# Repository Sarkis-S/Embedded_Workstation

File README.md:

# Embedded Workstation

A compact modular workstation for embedded systems development,
electronics prototyping, hardware testing, and PCB development.

## Current Revision

Rev A is the original acrylic workstation assembled as a practical
development platform rather than from a predefined mechanical design.

Current hardware includes:

- Arduino Uno
- ESP32 development platform
- Solderless breadboards
- Logic analyzer
- External bench power supply support
- Removable prototyping modules
- Two-level acrylic construction for equipment and cable management

## Design Goals

- Keep common embedded-development hardware readily accessible
- Provide a clean breadboarding and experimentation area
- Support both MCU-powered logic and externally powered loads
- Allow instrumentation such as a multimeter and logic analyzer to
  connect easily
- Remain modular so individual sections can be upgraded independently

## Development

The original workstation was designed and assembled iteratively.
Future modifications are being documented here as formal hardware
revisions.

Planned development includes:

- Workbench power interface
- Improved external power distribution
- Modular perfboard hardware
- Additional test points and connectors
- Future workstation revisions

### Workbench Power Interface

A custom perfboard-based external power distribution interface designed in KiCad for the workstation. The project includes physical perfboard modeling, component placement, realistic wiring planning, and documented design iterations.

See `hardware/workbench_power_interface/README.md` for the full design and lessons learned.

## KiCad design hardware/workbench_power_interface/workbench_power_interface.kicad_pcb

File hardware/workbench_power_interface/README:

```markdown
## Perfboard Design & Lessons Learned

The Workbench Power Interface started as a simple KiCad schematic and PCB layout, but adapting the design to a real 20 × 80 mm perfboard introduced a number of physical constraints that were not obvious during the initial electrical design.

### Designing for the Physical Perfboard

The available perfboard has:

- 20 × 80 mm physical dimensions
- 6 × 28 holes
- 2.54 mm hole pitch
- Isolated plated pads
- Four small M2 mounting holes

The original PCB layout was electrically correct, but it did not accurately represent the physical perfboard. This required revisiting the layout from a mechanical perspective.

A custom KiCad footprint was created to model the perfboard and provide a realistic placement reference.

### Building the Custom Perfboard Footprint

The footprint was designed around the actual 2.54 mm hole spacing.

Because the board contains an even number of rows and columns, its geometric center falls between holes rather than on a hole. The hole array therefore had to be positioned carefully relative to the 80 × 20 mm board outline.

The first version represented the perfboard holes as graphical circles. They were later changed to through-hole pads to more closely resemble the plated pads of the real perfboard.

This looked much more realistic and was useful for verifying component placement. However, it also introduced an important problem: KiCad treated the perfboard holes as real electrical pads.

When component pads were placed over the perfboard pads, the overlapping electrical geometry interfered with routing and connectivity.

This demonstrated an important distinction:

> A useful mechanical representation does not necessarily need to be an electrical representation.

The perfboard footprint will therefore be revised so that the hole pattern acts only as a visual and mechanical placement reference.

### Grid Alignment

The custom perfboard also demonstrated the importance of working with the physical manufacturing grid.

The perfboard uses standard 2.54 mm (0.1 inch) spacing. Setting the KiCad PCB grid to 2.54 mm allowed component footprints to align naturally with the physical hole pattern.

Several selected components are especially compatible with this spacing:

- 2.54 mm pin headers occupy adjacent perfboard holes.
- 5.08 mm terminal blocks span two perfboard pitches.
- The 10.16 mm resistor footprint spans four perfboard pitches.

Once the component layout was aligned to the 2.54 mm grid, the perfboard footprint was no longer required to determine component positions.

### PCB Routing vs. Perfboard Wiring

Another major change was how the connections were represented.

A conventional PCB can route copper traces freely around the board. The actual perfboard, however, uses isolated pads and must be connected manually using component leads, solder bridges, bus wire, or insulated hookup wire.

The layout was therefore revised to better represent how the board will actually be constructed.

Instead of using convenient diagonal PCB traces, the wiring was organized primarily as straight horizontal and vertical runs.

The KiCad routing is therefore being used as a **physical wiring plan**, rather than as artwork for manufactured copper traces.

### Key Lessons

This project demonstrated that passing electrical checks does not automatically make a design physically buildable.

Some of the lessons learned during the process were:

- Start with the dimensions and constraints of the real substrate.
- Electrical design and mechanical design must be considered together.
- Component lead pitch matters when designing for perfboard.
- A 2.54 mm grid provides a direct relationship between KiCad placement and real perfboard holes.
- Through-hole pads and graphical reference holes serve different purposes in KiCad.
- `Edge.Cuts` represents actual board geometry and should not be used merely as decorative artwork inside another PCB.
- Perfboard wiring must account for real wire paths, solder access, conductor size, and current.
- Empty perfboard space can intentionally remain available for future revisions.
- A clean schematic and DRC are only part of validating a physical design.

The biggest lesson was that the design process did not end when the schematic and PCB layout were complete. Inspecting the real hardware exposed new constraints, which required the digital model to be revised.

That iteration is now part of the workstation design process:

Requirements → Schematic → Layout → Physical Inspection → Revision → Build → Test
```

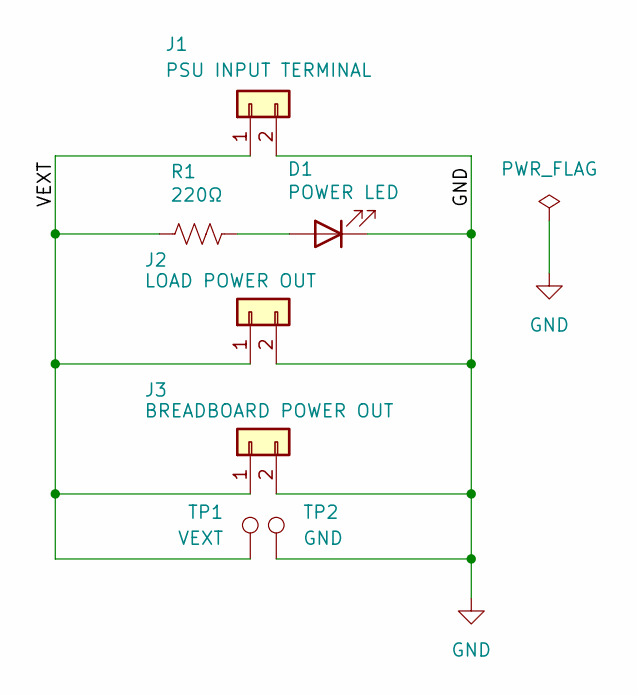
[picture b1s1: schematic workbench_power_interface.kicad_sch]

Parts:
D1: POWER LED; LED_D5.0mm
J1: PSU INPUT TERMINAL; TerminalBlock_Phoenix_MKDS-1,5-2-5.08_1x02_P5.08mm_Horizont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
J2: LOAD POWER OUT; TerminalBlock_Phoenix_MKDS-1,5-2-5.08_1x02_P5.08mm_Horizont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
J3: BREADBOARD POWER OUT; PinHeader_1x02_P2.54mm_Vertical
R1: 220Ω; R_Axial_DIN0207_L6.3mm_D2.5mm_P10.16mm_Horizontal
TP1: VEXT; TestPoint_THTPad_D2.0mm_Drill1.0mm
TP2: GND; TestPoint_THTPad_D2.0mm_Drill1.0mm

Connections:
/VEXT: J1.1, J2.1, J3.1, R1.1, TP1.1 (1_1)
GND: D1.1 (K), J1.2, J2.2, J3.2, TP2.1 (1_1)
unnamed: D1.2 (A), R1.2

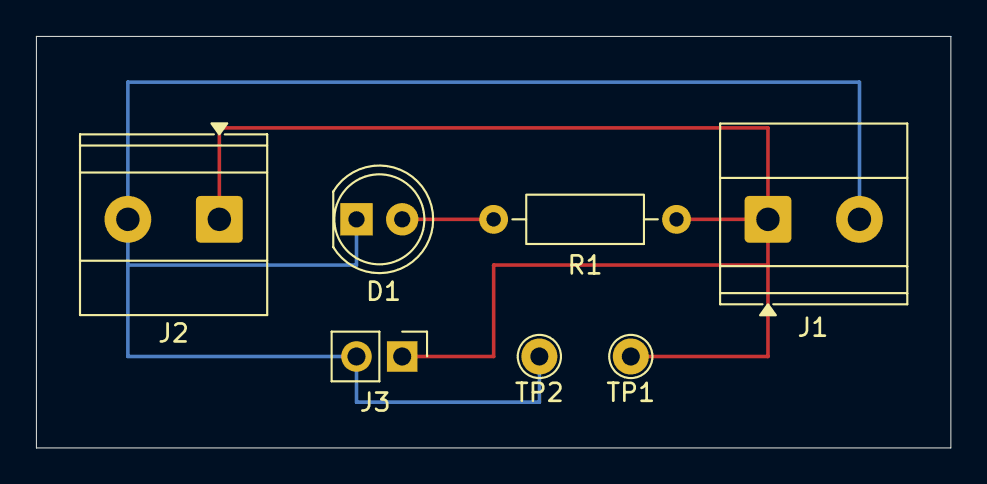
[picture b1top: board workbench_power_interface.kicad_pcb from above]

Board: 2 copper layers, 50.8 x 22.9 mm, 7 parts (0 on the bottom side), 3 nets.
